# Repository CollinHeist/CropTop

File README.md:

# CropTop
## Development
CropTop is a small-form data acquisition platform initially developed by Kennedy Caisley and Ryan Donahue, two undergraduate electrical engineering students at the University of Idaho. It is designed to support the cereal grain crop strength research being conducted by [Dr. Daniel Roberston](https://www.uidaho.edu/engr/departments/me/our-people/faculty/daniel-robertson) in the UI Department of Mechanical Engineering.

The current iteration of the project is being developed by [Collin Heist](https://github.com/CollinHeist), an undergraduate Electrical Engineering student at University of Idaho.

## What can CropTop do? 
Croptop is based around a 32 bit PIC32MX795F512L microcontroller and includes the following peripherals onboard:

* 12 bit temperature/humidity sensor
* 3-axis accelerometer
* ΔΣ 24 bit 1kSPS ADC
* GNSS receiver
* USB 2.0 OTG interface
* 5A DC motor controller
* Resistive touch controller
* Rotary encoder interface
* Linear encoder interface
* 1GB NAND flash
* User programmable push buttons
* User programmable LEDs
* 14 additional GPIO

The current screen and GUI utilizes the __[Nextion NX8048T070](https://nextion.tech/datasheets/nx8048t070/)__, which has an on-board graphical processor and memory. Interaction with the screen is done through a UART connection. The GUI is created using the Nextion GUI Editor, and has on-board code that can be interacted with using the Nextion-provided commands.

---

## To-Do

- [ ] Finish GPS implementation within `screen.c` and `GPS.c`
    - The interaction with the GPS is inside `screen.c`, but commented out. This is because the PIC would error during GPS read operations, and I was unable to diagnose why. I've since made some changes to the GPS library, and it might work but should be verified before implemented.
- [ ] Finish __refresh_live_feed__ command implementation in `screen.c`.
    - X-Load string needs to be generated and sent to display.
    - Y-Load string needs to be generated and sent to display.
    - Potentiometer angle string needs to be generated and sent to display.
    - IMU angle string needs to be generated and sent to display.
- [ ] Finish __start_test__ command implementation in `screen.c`.
    - The entire test procedure is not implemented.
    - Using `tests.c` is recommended, so that the test library is more comprehensive.
- [ ] Implement __stop_test__ command within `screen.c`.
    - Most likely, a FSM will need to be implemented to reflect the current _state_ of the PIC - i.e. __not_testing__, and __testing__ states inside `tests.c` to facilitate tests.
- [ ] Implement __view_first_folder__ command within `screen.c`.
    - This function will need to sent folder information data to the display. Currently not implemented since USB reading / writing is nonfunctional.
- [ ] Implement __view_next_folder__ command within `screen.c`.
    - This function will need to act similarly to __view_first_folder__, except sequence through folders on the USB.
- [ ] Implement test result graphing on the display.
    - This will need to be done with the `add` and `addt` commands (sent from PIC to display) for writing to the test results Waveform (graph). Read the Nextion Instruction Set description for more detail: https://nextion.tech/instruction-set/ .

---

## PCB Layout

### Version 1.0

Initial PCB design by Kennedy Caisley and Ryan Donahue.

### Version 2.0

Updated PCB design also by Kennedy Caisley and Ryan Donahue. This was more debuggable, and was designed to fit to the screen layout being used at the time (hence the shape). Had all the proper external connectors required for end-use. The screen connectors ended up being incorrectly aligned, and this required changing screen modules.

### Version 3.0

Latest PCB design, by Collin Heist, that removed the on-board graphics chip in favor of the Nextion 7" display header - but otherwise, the design from [v2.0](#pcb-v2) was preserved. The board was expanded to match the mounting holes provided by the Nextion screen.

---

## Code Development Standards

### Development Checklists

#### Header File

- [x] Has a valid file heading ([template](#templates-file-heading)).
- [x] Has multiple-inclusion protection ([template](#templates-inclusion-protection)).
- [x] Has verbose `#define` statements.
- [x] Has function prototypes.
- [x] Has limited (to no) macro functions - replace these with `inline` functions, instead.

#### Source File

- [x] Has an associated header file.
- [x] Has a valid file heading ([template](#templates-file-heading)).
- [x] Has required source file sections ([template](#templates-source-file-sections)).
- [x] All functions have an associated comment block ([template](#templates-source-file-sections)).
- [x] All _small_ functions, that will likely not require stepping through or debugging, are `inline`.
- [x] All function names and variables are verbose (i.e. `initialize_screen()` as opposed to `init_scr()`).
- [x] All function parameters that do not change during operation are `const`.
- [x] All functions that are not user-facing (from a library perspective) are private (`static`).

#### Nextion GUI

- [x] The number of unique pages are kept to a minimum because pages have quite a lot of overhead (in memory).
- [x] Objects with strings - either for text display or variables - have the minimum length required.
- [x] The number of PIC-screen communications are kept to a minimum this is because the UART communication is _somewhat_ unreliable.

-----

### Templates
#### File Heading (source and header)

```C
/**
 *  File
 *      filename.h
 *  Summary
 *      A brief summary of the header file's purpose.
 *  Author(s)
 *      Author 1, Author 2.
 *  Note
 *      Optional additional information regarding the file.
 */
```

#### Multiple Inclusion Protection

```C
#ifndef __FILENAME_H__
    #define __FILENAME_H__
    // Code
#endif
```

#### Source File Sections

```C
/* ----------------------------------- File Inclusion ----------------------------------- */
/* -------------------------- Global Variables and Structures --------------------------- */
/* ---------------------------------- Public Functions ---------------------------------- */
/* --------------------------------- Private Functions ---------------------------------- */
/* ----------------------------- Interrupt Service Routines ----------------------------- */
```

#### Function Comment Blocks

```C
/*
 *  Summary
 *      Short description of the function.
 *  Parameters
 *      param1[in]: Description of the first parameter (in if not changed).
 *      param2[out]: Description of the second parameter (out if changed).
 *  Returns
 *      Describe the meaning of the return value (if there is one).
 *  Note
 *      Optional addition of the function.
 */
```

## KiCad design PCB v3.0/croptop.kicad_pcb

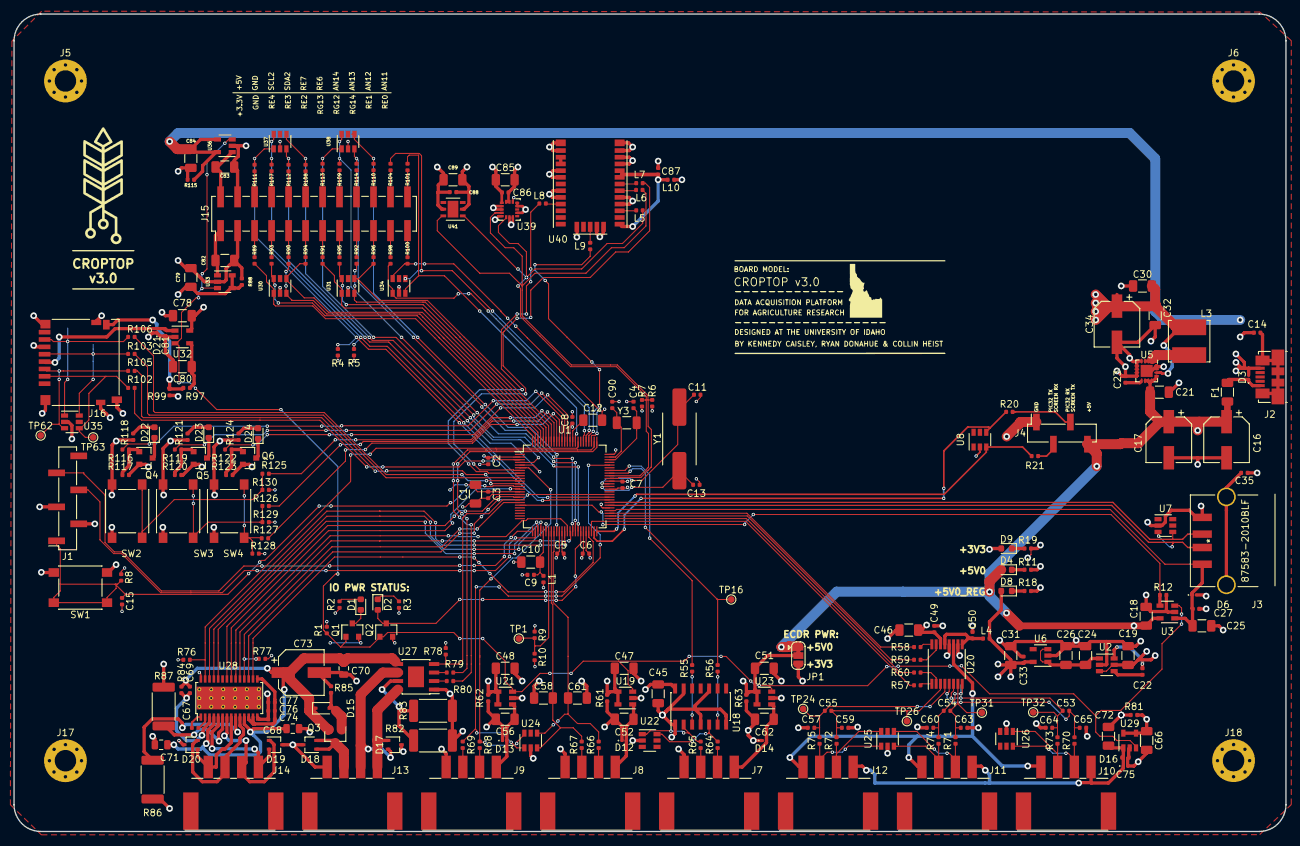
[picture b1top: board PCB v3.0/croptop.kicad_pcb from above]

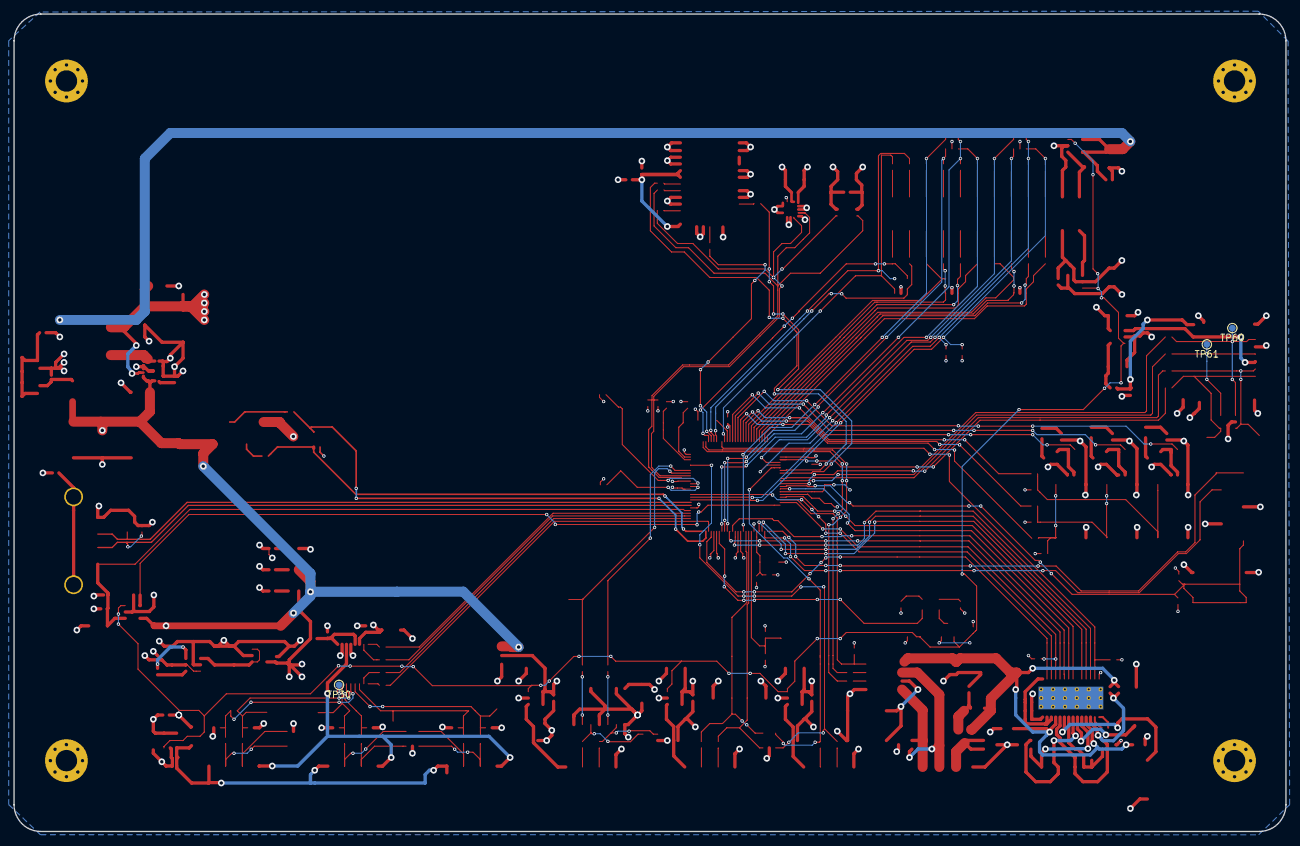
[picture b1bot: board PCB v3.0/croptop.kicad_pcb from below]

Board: 4 copper layers, 190.1 x 122.2 mm, 274 parts (3 on the bottom side), 196 nets.

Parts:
 : idaho
C1, C10, C12, C18, C19, C21, C24, C25, C26, C30, C31, C32, C45, C46, C47, C48, C51, C52, C56, C58, C61, C62, C66, C72, C78, C79, C80, C82, C83, C84, C85, C89: 10u; C_1206_3216Metric
C2, C3, C5, C6, C7, C8, C9, C14, C15, C22, C23, C27, C33, C35, C49, C50, C53, C54, C55, C57, C59, C60, C63, C64, C65, C69, C74, C75, C76, C77, C81, C86, C87, C88: 0.1u; C_0402_1005Metric
C4, C90: 12.5p; C_0402_1005Metric
C11, C13: 27p; C_0402_1005Metric
C16, C17, C34, C73: 100u; CP_Elec_6.3x7.7
C67: 0.01u; C_0402_1005Metric
C68, C70, C71: 0.1u; C_0805_2012Metric
D1, D4, D8, D9, D22, D23, D24: LTSTC190KGKT; LED_0603_1608Metric
D2: LTSTC190KRKT; LED_0603_1608Metric
D3, D6, D12, D13, D14, D16, D21: TPD1E6B06; D_0201_0603Metric
D15: NSR0240HT1G; D_SOD-323
D17, D18, D19, D20: TPD2E007; SOT-323_SC-70
F1: MF-NSMF110; Fuse_1206_3216Metric
J1: TSM-106-01-L-SV; PinHeader_1x06_P2.54mm_Vertical_SMD_Pin1Right
J2: 0473460001; USB_Micro-B_Molex_47346-0001
J3: 87583-2010BLF
J4: NREC004SABC-M30RC; PinHeader_1x04_P2.54mm_Vertical_SMD_Pin1Right
J5, J6, J17, J18: Conn_01x01; MountingHole_3.2mm_M3_Pad_Via
J7, J8, J9, J10, J11, J12, J13, J14: 1702474; solderless_terminal
J15: TSM-112-01-L-DV; PinHeader_2x12_P2.54mm_Vertical_SMD
J16: DM3D-SF; microSD_HC_Hirose_DM3D-SF
JP1: Solder Jumper; SolderJumper-3_P1.3mm_Bridged12_RoundedPad1.0x1.5mm
L1, L4, L10: BKP1005HS121; L_0402_1005Metric
L3: 2.2u; L_Bourns_SRN6045TA
L5, L6, L7, L8, L9: BLM15HD102SN1D; L_0402_1005Metric
Q1, Q4, Q5, Q6: BSS138; SOT-23
Q2: BSS84; SOT-23
Q3: Q2319ADS-T1-GE3; SOT-23
R1, R4, R5, R6, R7, R8, R9, R10, R12, R61, R62, R63, R76, R77, R78, R81, R85, R88, R99, R115, R117, R120, R123, R125, R126, R127, R128, R129, R130: 10k; R_0402_1005Metric
R2, R3, R19, R70, R71, R72, R73, R74, R75, R116, R118, R119, R121, R122, R124: 100; R_0402_1005Metric
R11, R18, R20, R21, R64, R65, R66, R67, R68, R69, R89, R90, R91, R92, R93, R94, R95, R96, R97, R98, R100, R101, R104, R107, R108, R109, R110, R111, R112, R113, R114: 220; R_0402_1005Metric
R55, R56, R57, R58, R59, R60, R79, R80, R102, R103, R105, R106: 22; R_0402_1005Metric
R82, R83, R86, R87: 0.2; R_2512_6332Metric
R84: 1M; R_0402_1005Metric
SW1, SW2, SW3, SW4: SW_Push; SW_SPST_PTS645
TP1, TP16, TP24, TP26, TP30, TP31, TP32, TP60, TP61, TP62, TP63: TestPoint; TestPoint_Pad_D1.0mm
U1: PIC32MX795F512L; TQFP-100_12x12mm_P0.4mm
U2: REG71055DDC; SOT-23-6
U3, U19, U21, U23, U29, U32, U33, U36: AP22802AW5; SOT-23-5
U5: TPS62131RGT; QFN-16-1EP_3x3mm_P0.5mm_EP1.8x1.8mm
U6: TPS70950DBV; SOT-23-5
U7, U8, U22, U24, U25, U26, U30, U31, U34, U35, U37, U38: TPD4E1U06DBV; SOT-23-6
U18: 74HCT125D653; SOIC-14_3.9x8.7mm_P1.27mm
U20: AD7799; TSSOP-16_4.4x5mm_P0.65mm
U27: DRV8872; 8-PowerSOIC
U28: DRV8825; HTSSOP-28-1EP_4.4x9.7mm_P0.65mm_EP3.4x9.5mm_Mask2.4x6.17mm_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
U39: LIS3DSHTR; LISDR
U40: CAM-M8C-0; GPS
U41: Si7006-A20; SI7006
Y1: ABLS-8.000MHZ-B4-T; ABLS_OX
Y3: ABS07-32.768KHZ-1-T; ABLS_SEC

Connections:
+3V3: C1.1, C2.1, C3.1, C5.1, C6.1, C7.1, C8.1, C30.1, C32.1, C34.1, C45.1, C46.1, C47.1, C48.1, C49.1, C78.1, C79.1, C85.1, C86.1, C88.1, C89.1, D9.2, J1.2, J16.10, JP1.3, L1.1, L3.1, L10.1, Q2.2, R1.1, R2.2, R4.1, R5.1, R6.1, R7.1, R8.1, R9.1, R61.1, R62.1, R76.1, R77.1, R78.1, R88.1, R118.2, R121.2, R124.2, SW2.2, SW3.2, SW4.2, U1.2, U1.16, U1.37, U1.46, U1.55, U1.62, U1.86, U5.14, U18.14, U19.4, U19.5, U20.14, U21.4, U21.5, U32.5, U33.4, U33.5, U39.1, U39.7, U39.8, U39.14, U41.5
+5V: C16.1, C17.1, C18.1, C19.1, C21.1, C84.1, D4.2, F1.1, J4.4, JP1.1, R115.1, U2.3, U2.5, U3.5, U5.10, U5.11, U5.12, U5.13, U36.4, U36.5
+5V_REG: C31.1, C33.1, C66.1, D8.2, L4.2, R81.1, U6.5, U29.4, U29.5
ADI_A1+: J10.2, R70.1, U26.6
ADI_A1-: J10.3, R73.1, U26.1
ADI_A2+: J11.2, R71.1, U25.4
ADI_A2-: J11.3, R74.1, U25.3
ADI_A3+: J12.2, R72.1, U25.6
ADI_A3-: J12.3, R75.1, U25.1
ADI_MISO: R59.2, U1.52
ADI_MOSI: R58.2, U1.53
ADI_PSW: J10.4, J11.4, J12.4, U20.11
ADI_SCLK: R57.2, U1.48
CONFIG_ADC: R9.2, R10.1, TP1.1, U1.32
DC_PWM_1: R79.2, U1.76
DC_PWM_2: R80.2, U1.77
DEBUG_BTN_1: R125.1, U1.92
DEBUG_BTN_2: R126.1, U1.91
DEBUG_BTN_3: R127.1, U1.90
DEBUG_LED_1: R116.1, U1.89
DEBUG_LED_2: R119.1, U1.88
DEBUG_LED_3: R122.1, U1.87
DGND: C1.2, C2.2, C3.2, C4.2, C5.2, C6.2, C7.2, C8.2, C9.2, C10.2, C11.2, C12.2, C13.2, C14.2, C15.2, C16.2, C17.2, C18.2, C19.2, C21.2, C23.2, C24.2, C25.2, C26.2, C27.2, C30.2, C31.2, C32.2, C33.2, C34.2, C35.1, C45.2, C46.2, C47.2, C48.2, C49.2, C50.2, C51.2, C52.2, C56.2, C57.1, C58.2, C59.1, C60.1, C61.2, C62.2, C63.1, C64.1, C65.1, C66.2, C68.2, C70.2, C71.2, C72.2, C73.2, C74.2, C75.1, C76.2, C77.2, C78.2, C79.2, C80.2, C81.2, C82.2, C83.2, C84.2, C85.2, C86.2, C87.2, C88.2, C89.2, C90.2, D3.2, D6.2, D12.1, D13.1, D14.1, D16.2, D17.3, D18.3, D19.3, D20.3, D21.1, J1.3, J2.5, J3.4, J4.1, J5.1, J6.1, J7.4, J8.4, J9.4, J13.4, J15.3, J15.4, J16.6, J16.11, J17.1, J18.1, Q1.2, Q4.2, Q5.2, Q6.2, R3.2, R10.2, R11.2, R12.2, R18.2, R19.2, R61.2, R62.2, R63.2, R81.2, R82.2, R83.2, R85.2, R86.2, R87.2, R88.2, R99.2, R115.2, R117.2, R120.2, R123.2, R128.2, R129.2, R130.2, SW1.2, U1.15, U1.31, U1.36, U1.45, U1.65, U1.75, U2.2, U3.2, U5.4, U5.5, U5.6, U5.7, U5.8, U5.15, U5.16, U5.17, U6.2, U7.2, U8.2, U18.1, U18.4, U18.7, U18.10, U18.13, U19.2, U20.10, U20.12, U21.2, U22.2, U23.2, U24.2, U25.2, U26.2, U27.1, U28.14, U28.28, U29.2, U30.2, U31.2, U32.2, U33.2, U34.2, U35.2, U36.2, U37.2, U38.2, U39.2, U39.3, U39.5, U39.10, U39.12, U39.13, U39.15, U39.16, U40.4, U40.5, U40.10, U40.11, U40.12, U40.13, U40.14, U40.15, U40.18, U40.19, U40.21, U40.22, U40.27, U40.30, U40.31, U41.2
ENCDR_A: R56.2, TP16.1, U1.68
ENCDR_B: R55.2, U1.69
GPS_EXTINT: L7.1, U1.7
GPS_PPS: L9.1, U1.79
unnamed: C4.1, U1.73, Y3.1
unnamed: C9.1, C10.1, L1.2, U1.30
unnamed: C11.1, U1.64, Y1.2
unnamed: C12.1, U1.85
unnamed: C13.1, U1.63, Y1.1
unnamed: C14.1, J2.6
unnamed: C22.1, U2.6
unnamed: C22.2, U2.4
unnamed: C23.1, U5.9
unnamed: C24.1, C26.1, U2.1, U6.1, U6.3
unnamed: C35.2, J3.5
unnamed: C50.1, L4.1, U20.9, U20.13
unnamed: C51.1, JP1.2, R63.1, U23.4, U23.5
unnamed: C52.1, D12.2, J8.1, U19.1
unnamed: C53.1, C64.2, R73.2, TP32.1, U20.6
unnamed: C53.2, C65.2, R70.2, U20.5
unnamed: C54.1, C60.2, R74.2, TP30.1, U20.8
unnamed: C54.2, C63.2, R71.2, TP31.1, U20.7
unnamed: C55.1, C57.2, R75.2, TP24.1, U20.4
unnamed: C55.2, C59.2, R72.2, TP26.1, U20.3
unnamed: C56.1, D13.2, J9.1, U21.1
unnamed: C62.1, D14.2, J7.1, U23.1
unnamed: C67.1, U28.2
unnamed: C67.2, U28.1
unnamed: C68.1, C69.2, C70.1, C71.1, C73.1, D15.1, Q3.2, R84.1, U27.5, U28.4, U28.11
unnamed: C69.1, R84.2, U28.3
unnamed: C72.1, C75.2, D16.1, J10.1, J11.1, J12.1, U29.1
unnamed: C74.1, C76.1, C77.1, U28.12, U28.13, U28.15
unnamed: C80.1, R97.2, U32.4
unnamed: C81.1, D21.2, J16.4, U32.1
unnamed: C82.1, J15.1, U33.1
unnamed: C83.1, J15.2, U36.1
unnamed: C87.1, L10.2, U40.1, U40.8, U40.9
unnamed: C90.1, U1.74, Y3.2
unnamed: D1.1, Q1.3
unnamed: D1.2, R2.1
unnamed: D2.1, R3.1
unnamed: D2.2, Q2.3, U1.44
unnamed: D3.1, F1.2, J2.1
unnamed: D4.1, R11.1
unnamed: D8.1, R18.1
unnamed: D9.1, R19.1
unnamed: D15.2, Q3.1, R85.1
unnamed: D17.1, J13.1, U27.8
unnamed: D17.2, J13.2, U27.6
unnamed: D18.1, D18.2, J13.3, Q3.3
unnamed: D19.1, J14.2, U28.7
unnamed: D19.2, J14.1, U28.5
unnamed: D20.1, J14.4, U28.8
unnamed: D20.2, J14.3, U28.10
unnamed: D22.1, Q4.3
unnamed: D22.2, R118.1
unnamed: D23.1, Q5.3
unnamed: D23.2, R121.1
unnamed: D24.1, Q6.3
unnamed: D24.2, R124.1
unnamed: J4.2, R21.2
unnamed: J4.3, R20.2
unnamed: J7.2, R64.1
unnamed: J7.3, R65.1
unnamed: J8.2, R66.1
unnamed: J8.3, R67.1
unnamed: J9.2, R68.1
unnamed: J9.3, R69.1
unnamed: J15.5, R89.2
unnamed: J15.6, R111.2
unnamed: J15.7, R93.2
unnamed: J15.8, R107.2
unnamed: J15.9, R90.2
unnamed: J15.10, R112.2
unnamed: J15.11, R94.2
unnamed: J15.12, R108.2
unnamed: J15.13, R91.2
unnamed: J15.14, R113.2
unnamed: J15.15, R95.2
unnamed: J15.16, R109.2
unnamed: J15.17, R92.2
unnamed: J15.18, R114.2
unnamed: J15.19, R96.2
unnamed: J15.20, R110.2
unnamed: J15.21, R98.2
unnamed: J15.22, R104.2
unnamed: J15.23, R100.2
unnamed: J15.24, R101.2
unnamed: J16.2, R102.1, TP63.1, U35.4
unnamed: J16.3, R105.1, TP62.1, U35.3
unnamed: J16.5, R103.1, TP61.1, U35.6
unnamed: J16.7, R106.1, TP60.1, U35.1
unnamed: J16.9, R97.1, R99.1
unnamed: L3.2, U5.1, U5.2, U5.3
unnamed: L5.2, U40.3
unnamed: L6.2, U40.6
unnamed: L7.2, U40.7
unnamed: L8.2, U40.23
unnamed: L9.2, U40.29
unnamed: Q4.1, R116.2, R117.1
unnamed: Q5.1, R119.2, R120.1
unnamed: Q6.1, R122.2, R123.1
unnamed: R55.1, U18.3
unnamed: R56.1, U18.6
unnamed: R57.1, U20.1
unnamed: R58.1, U20.16
unnamed: R59.1, U20.15
unnamed: R60.1, U20.2
unnamed: R64.2, U18.5, U22.6
unnamed: R65.2, U18.2, U22.1
unnamed: R79.1, U27.3
unnamed: R80.1, U27.2
unnamed: R82.1, R83.1, U27.7
unnamed: R86.1, U28.9
unnamed: R87.1, U28.6
unnamed: R125.2, R130.1, SW2.1
unnamed: R126.2, R129.1, SW3.1
unnamed: R127.2, R128.1, SW4.1
unnamed: U40.16, U40.17
ONBRD_SCL: L6.1, R6.2, U1.66, U39.4, U41.6
ONBRD_SDA: L5.1, R7.2, U1.67, U39.6, U41.1
PICKIT_MCLR: C15.1, J1.1, R8.2, SW1.1, U1.13
PICKIT_PGEC: J1.5, U1.26
PICKIT_PGED: J1.4, U1.27
PMOD_ADC_1: R110.1, U1.35, U38.4
PMOD_ADC_2: R114.1, U1.41, U38.3
PMOD_ADC_3: R109.1, U1.42, U38.6
PMOD_ADC_4: R113.1, U1.43, U38.1
PMOD_CN_1: R101.1, U1.84, U34.3
PMOD_CN_2: R104.1, U1.80, U34.4
PMOD_GPIO_1: R96.1, U1.93, U31.4
PMOD_GPIO_2: R92.1, U1.94, U31.3
PMOD_GPIO_3: R95.1, U1.95, U31.6
PMOD_GPIO_4: R91.1, U1.96, U31.1
PMOD_GPIO_5: R94.1, U1.97, U30.4
PMOD_GPIO_6: R90.1, U1.98, U30.3
PMOD_GPIO_7: R93.1, U1.99, U30.6
PMOD_GPIO_8: R89.1, U1.100, U30.1
PMOD_GPIO_9: R108.1, U1.4, U37.4
PMOD_GPIO_10: R112.1, U1.5, U37.3
PMOD_PWM_1: R100.1, U1.78, U34.6
PMOD_PWM_2: R98.1, U1.81, U34.1
PMOD_SCL: R4.2, R111.1, U1.58, U37.1
PMOD_SDA: R5.2, R107.1, U1.59, U37.6
POTEN_ADC_1: C61.1, R66.2, U1.34, U24.4
POTEN_ADC_2: C58.1, R67.2, U1.33, U24.3
SCREEN_RX: R20.1, U1.49, U8.4
SCREEN_TX: R21.1, U1.50, U8.3
SD_MISO: R106.2, U1.11
SD_MOSI: R105.2, U1.12
SD_SCLK: R103.2, U1.10
SONIC_ECHO: R69.2, U1.71, U24.1
SONIC_TRIG: R68.2, U1.6, U24.6
STEP_DECAY: U1.40, U28.19
STEP_DIR: U1.39, U28.20
STEP_MODE0: U1.28, U28.24
STEP_MODE1: U1.29, U28.25
STEP_MODE2: U1.38, U28.26
STEP_STEP: U1.17, U28.22
USB_D+: J3.3, U1.57, U7.4
USB_D-: J3.2, U1.56, U7.3
USB_PWR_EN: R12.1, U1.20, U3.4
USB_PWR_SENSE: C25.1, C27.1, D6.1, J3.1, U1.54, U3.1
~ADI_CS: R60.2, U1.51
~DC_FAULT: R78.2, U1.18, U27.4
~GPS_RESET: L8.1, U1.8
~PWR_FAULT: Q1.1, Q2.1, R1.2, U3.3, U19.3, U21.3, U23.3, U29.3, U32.3, U33.3, U36.3
~SD_CS: R102.2, U1.3
~STEP_ENBL: U1.14, U28.21
~STEP_FAULT: R77.2, U1.19, U28.18
~STEP_HOME: R76.2, U1.83, U28.27
~STEP_RESET: U1.60, U28.17
~STEP_SLEEP: U1.47, U28.16

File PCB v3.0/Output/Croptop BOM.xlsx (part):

Reference | Value | Footprint | Datasheet | MPN | Note | Rating
C17 | 100u | Capacitor_SMD:CP_Elec_6.3x7.7 |  | EEE-HC1C101XP
U2 | REG71055DDC | Package_TO_SOT_SMD:SOT-23-6 | http://www.ti.com/lit/ds/symlink/reg71050.pdf | REG71055DDCT
L3 | 2.2u | Inductor_SMD:L_Bourns_SRN6045TA | https://www.bourns.com/docs/Product-Datasheets/SRN8040.pdf | SRN6045TA-2R2Y
C21 | 10u | Capacitor_SMD:C_1206_3216Metric |  | CC1206ZRY5V6BB106
C22 | 0.1u | Capacitor_SMD:C_0402_1005Metric |  | CL05F104ZO5NNNC
C31 | 10u | Capacitor_SMD:C_1206_3216Metric |  | CC1206ZRY5V6BB106
J2 | 473460001 | Connector_USB:USB_Micro-B_Molex_47346-0001 | https://www.amphenol-icc.com/media/wysiwyg/files/drawing/101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 | 473460001 | microUSB B
D9 | LTSTC190KGKT | LED_SMD:LED_0603_1608Metric |  | LTST-C190KGKT
R19 | 100 | Resistor_SMD:R_0402_1005Metric |  | RC0402FR-07100RL
D8 | LTSTC190KGKT | LED_SMD:LED_0603_1608Metric |  | LTST-C190KGKT
R18 | 220 | Resistor_SMD:R_0402_1005Metric |  | CRGCQ0402F220R
C16 | 100u | Capacitor_SMD:CP_Elec_6.3x7.7 |  | EEE-HC1C101XP
C34 | 100u | Capacitor_SMD:CP_Elec_6.3x7.7 |  | EEE-HC1C101XP
D4 | LTSTC190KGKT | LED_SMD:LED_0603_1608Metric |  | LTST-C190KGKT
R11 | 220 | Resistor_SMD:R_0402_1005Metric |  | CRGCQ0402F220R
U5 | TPS62131RGT | Package_DFN_QFN:QFN-16-1EP_3x3mm_P0.5mm_EP1.8x1.8mm | http://www.ti.com/lit/ds/symlink/tps62130.pdf | TPS62131RGTT
C23 | 0.1u | Capacitor_SMD:C_0402_1005Metric |  | CL05F104ZO5NNNC
U6 | TPS70950DBV | Package_TO_SOT_SMD:SOT-23-5 | http://www.ti.com/lit/ds/symlink/tps709.pdf | TPS70950DBVR
C26 | 10u | Capacitor_SMD:C_1206_3216Metric |  | CC1206ZRY5V6BB106
C19 | 10u | Capacitor_SMD:C_1206_3216Metric |  | CC1206ZRY5V6BB106
C24 | 10u | Capacitor_SMD:C_1206_3216Metric |  | CC1206ZRY5V6BB106
C30 | 10u | Capacitor_SMD:C_1206_3216Metric |  | CC1206ZKY5V7BB106 |  | 16V
C32 | 10u | Capacitor_SMD:C_1206_3216Metric |  | CC1206ZRY5V6BB106
C33 | 0.1u | Capacitor_SMD:C_0402_1005Metric |  | CL05F104ZO5NNNC
D3 | TPD1E6B06 | Diode_SMD:D_0201_0603Metric |  | TPD1E6B06DPLR
C1 | 10u | Capacitor_SMD:C_1206_3216Metric |  | CC1206ZRY5V6BB106
C2 | 0.1u | Capacitor_SMD:C_0402_1005Metric |  | CL05F104ZO5NNNC
C3 | 0.1u | Capacitor_SMD:C_0402_1005Metric |  | CL05F104ZO5NNNC
C5 | 0.1u | Capacitor_SMD:C_0402_1005Metric |  | CL05F104ZO5NNNC
C6 | 0.1u | Capacitor_SMD:C_0402_1005Metric |  | CL05F104ZO5NNNC
C7 | 0.1u | Capacitor_SMD:C_0402_1005Metric |  | CL05F104ZO5NNNC
C8 | 0.1u | Capacitor_SMD:C_0402_1005Metric |  | CL05F104ZO5NNNC
C12 | 10u | Capacitor_SMD:C_1206_3216Metric |  | CC1206ZRY5V6BB106
R4 | 10k | Resistor_SMD:R_0402_1005Metric |  | RC0402FR-0710KL
R5 | 10k | Resistor_SMD:R_0402_1005Metric |  | RC0402FR-0710KL
L1 | BKP1005HS121 | Inductor_SMD:L_0402_1005Metric |  | BKP1005HS121-TV
C9 | 0.1u | Capacitor_SMD:C_0402_1005Metric |  | CL05F104ZO5NNNC
C10 | 10u | Capacitor_SMD:C_1206_3216Metric |  | CC1206ZRY5V6BB106
R8 | 10k | Resistor_SMD:R_0402_1005Metric |  | RC0402FR-0710KL
C15 | 0.1u | Capacitor_SMD:C_0402_1005Metric |  | CL05F104ZO5NNNC
J1 | TSM-106-01-L-SV | Connector_PinHeader_2.54mm:PinHeader_1x06_P2.54mm_Vertical_SMD_Pin1Right | http://suddendocs.samtec.com/prints/tsm-1xx-xx-xxx-sv-xx-xxx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 | TSM-106-01-L-SV
SW1 | SW_Push | Button_Switch_SMD:SW_SPST_PTS645 |  | PTS645SM43SMTR92 LFS
R9 | 10k | Resistor_SMD:R_0402_1005Metric |  | RC0402FR-0710KL
R10 | 10k | Resistor_SMD:R_0402_1005Metric |  | RC0402FR-0710KL
J3 | 87583-2010BLF | croptop:87583-2010BLF |  | 87583-2010BLF | USB A
U7 | TPD4E1U06DBV | Package_TO_SOT_SMD:SOT-23-6 | http://www.ti.com/lit/ds/symlink/tpd4e1u06.pdf | TPD4E1U06DBVR
C18 | 10u | Capacitor_SMD:C_1206_3216Metric |  | CC1206ZRY5V6BB106
U3 | AP22802AW5 | Package_TO_SOT_SMD:SOT-23-5 | https://www.diodes.com/assets/Datasheets/AP22802.pdf | AP22802AW5-7
R12 | 10k | Resistor_SMD:R_0402_1005Metric |  | RC0402FR-0710KL
C25 | 10u | Capacitor_SMD:C_1206_3216Metric |  | CC1206ZRY5V6BB106
C27 | 0.1u | Capacitor_SMD:C_0402_1005Metric |  | CL05F104ZO5NNNC
U1 | PIC32MX795F512L | Package_QFP:TQFP-100_12x12mm_P0.4mm | http://www.microchip.com/mymicrochip/filehandler.aspx?ddocna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 | PIC32MX795F512LT-80I/PT
Y1 | ABLS-8.000MHZ-B4-T | croptop:ABLS_OX |  | ABLS-8.000MHZ-B4-T
C13 | 27p | Capacitor_SMD:C_0402_1005Metric |  | C0402C270K5GACTU
C11 | 27p | Capacitor_SMD:C_0402_1005Metric |  | C0402C270K5GACTU
R6 | 10k | Resistor_SMD:R_0402_1005Metric |  | RC0402FR-0710KL
R7 | 10k | Resistor_SMD:R_0402_1005Metric |  | RC0402FR-0710KL
D6 | TPD1E6B06 | Diode_SMD:D_0201_0603Metric |  | TPD1E6B06DPLR
C35 | 0.1u | Capacitor_SMD:C_0402_1005Metric |  | CL05F104ZO5NNNC
C14 | 0.1u | Capacitor_SMD:C_0402_1005Metric |  | CL05F104ZO5NNNC
R1 | 10k | Resistor_SMD:R_0402_1005Metric |  | RC0402FR-0710KL
Q1 | BSS138 | Package_TO_SOT_SMD:SOT-23 |  | BSS138-TP
R2 | 100 | Resistor_SMD:R_0402_1005Metric |  | RC0402FR-07100RL
D1 | LTSTC190KGKT | LED_SMD:LED_0603_1608Metric |  | LTST-C190KGKT
Q2 | BSS84 | Package_TO_SOT_SMD:SOT-23 | ~ | BSS84
D2 | LTSTC190KRKT | LED_SMD:LED_0603_1608Metric |  | LTST-C190KRKT
R3 | 100 | Resistor_SMD:R_0402_1005Metric |  | RC0402FR-07100RL
F1 | MF-NSMF110 | Fuse:Fuse_1206_3216Metric | ~ | MF-NSMF110-2
Y3 | ABS07-32.768KHZ-1-T | croptop:ABLS_SEC | https://www.digikey.com/product-detail/en/abracon-llc/ABS07-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 | ABS07-32.768KHZ-1-T
C4 | 12.5p | Capacitor_SMD:C_0402_1005Metric |  | CC0402JRNPO9BN120
C90 | 12.5p | Capacitor_SMD:C_0402_1005Metric |  | CC0402JRNPO9BN120
J4 | NREC004SABC-M30RC | Connector_PinHeader_2.54mm:PinHeader_1x04_P2.54mm_Vertical_SMD_Pin1Right | https://drawings-pdf.s3.amazonaws.com/11657.pdf | NREC004SABC-M30RC
U8 | TPD4E1U06DBV | Package_TO_SOT_SMD:SOT-23-6 | http://www.ti.com/lit/ds/symlink/tpd4e1u06.pdf | TPD4E1U06DBVR
R20 | 220 | Resistor_SMD:R_0402_1005Metric |  | CRGCQ0402F220R
R21 | 220 | Resistor_SMD:R_0402_1005Metric |  | CRGCQ0402F220R
U27 | DRV8872 | croptop:8-PowerSOIC | http://www.ti.com/lit/ds/symlink/drv8872.pdf | DRV8872DDAR
C46 | 10u | Capacitor_SMD:C_1206_3216Metric |  | CC1206ZRY5V6BB106
C49 | 0.1u | Capacitor_SMD:C_0402_1005Metric |  | CL05F104ZO5NNNC
U20 | AD7799 | Package_SO:TSSOP-16_4.4x5mm_P0.65mm | https://www.analog.com/media/en/technical-documentation/data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 | AD7799BRUZ
C50 | 0.1u | Capacitor_SMD:C_0402_1005Metric |  | CL05F104ZO5NNNC
C59 | 0.1u | Capacitor_SMD:C_0402_1005Metric |  | CL05F104ZO5NNNC
C63 | 0.1u | Capacitor_SMD:C_0402_1005Metric |  | CL05F104ZO5NNNC
C60 | 0.1u | Capacitor_SMD:C_0402_1005Metric |  | CL05F104ZO5NNNC
C65 | 0.1u | Capacitor_SMD:C_0402_1005Metric |  | CL05F104ZO5NNNC
C64 | 0.1u | Capacitor_SMD:C_0402_1005Metric |  | CL05F104ZO5NNNC
C57 | 0.1u | Capacitor_SMD:C_0402_1005Metric |  | CL05F104ZO5NNNC
C70 | 0.1u | Capacitor_SMD:C_0805_2012Metric |  | C0805C104Z5VACTU
D15 | NSR0240HT1G | Diode_SMD:D_SOD-323 |  | NSR0240HT1G
C73 | 100u | Capacitor_SMD:CP_Elec_6.3x7.7 |  | UWT1V101MCL1GS |  | 35V
C67 | 0.01u | Capacitor_SMD:C_0402_1005Metric | https://www.digikey.com/product-detail/en/samsung-electro-me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 | CC0402KRX7R9BB103 |  | 50V
R78 | 10k | Resistor_SMD:R_0402_1005Metric |  | RC0402FR-0710KL
R79 | 22 | Resistor_SMD:R_0402_1005Metric |  | RC0402FR-0722RL
R80 | 22 | Resistor_SMD:R_0402_1005Metric |  | RC0402FR-0722RL
R85 | 10k | Resistor_SMD:R_0402_1005Metric |  | RC0402FR-0710KL
R76 | 10k | Resistor_SMD:R_0402_1005Metric |  | RC0402FR-0710KL
R77 | 10k | Resistor_SMD:R_0402_1005Metric |  | RC0402FR-0710KL
R60 | 22 | Resistor_SMD:R_0402_1005Metric |  | RC0402FR-0722RL
R59 | 22 | Resistor_SMD:R_0402_1005Metric |  | RC0402FR-0722RL
R58 | 22 | Resistor_SMD:R_0402_1005Metric |  | RC0402FR-0722RL
R57 | 22 | Resistor_SMD:R_0402_1005Metric |  | RC0402FR-0722RL
R70 | 100 | Resistor_SMD:R_0402_1005Metric |  | RC0402FR-07100RL
R73 | 100 | Resistor_SMD:R_0402_1005Metric |  | RC0402FR-07100RL
R71 | 100 | Resistor_SMD:R_0402_1005Metric |  | RC0402FR-07100RL
R74 | 100 | Resistor_SMD:R_0402_1005Metric |  | RC0402FR-07100RL
R72 | 100 | Resistor_SMD:R_0402_1005Metric |  | RC0402FR-07100RL
R75 | 100 | Resistor_SMD:R_0402_1005Metric |  | RC0402FR-07100RL
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
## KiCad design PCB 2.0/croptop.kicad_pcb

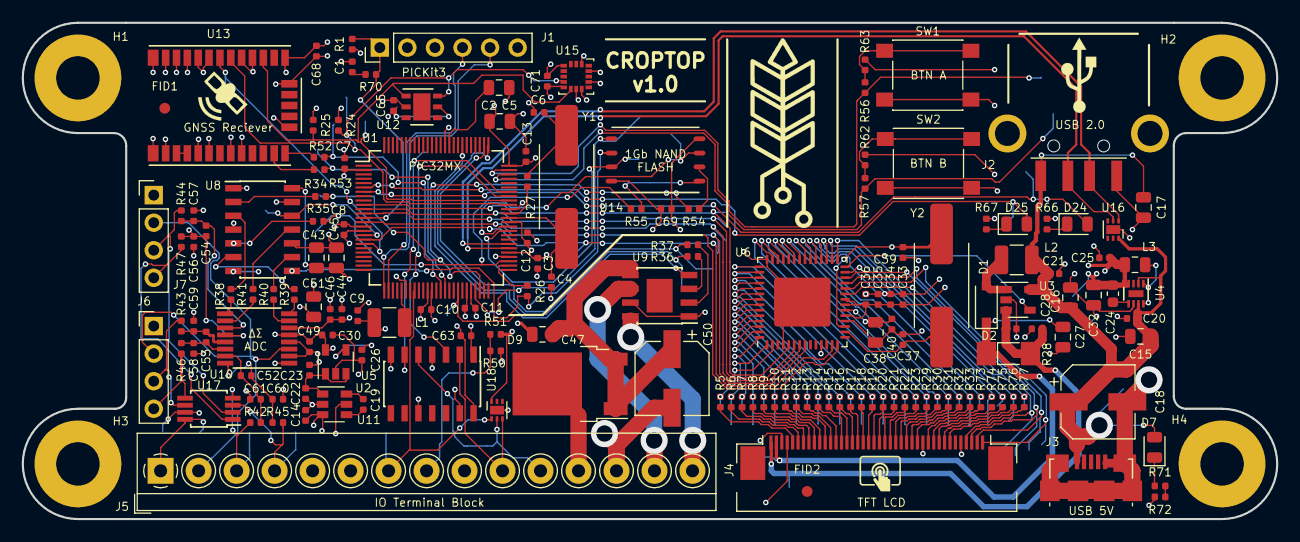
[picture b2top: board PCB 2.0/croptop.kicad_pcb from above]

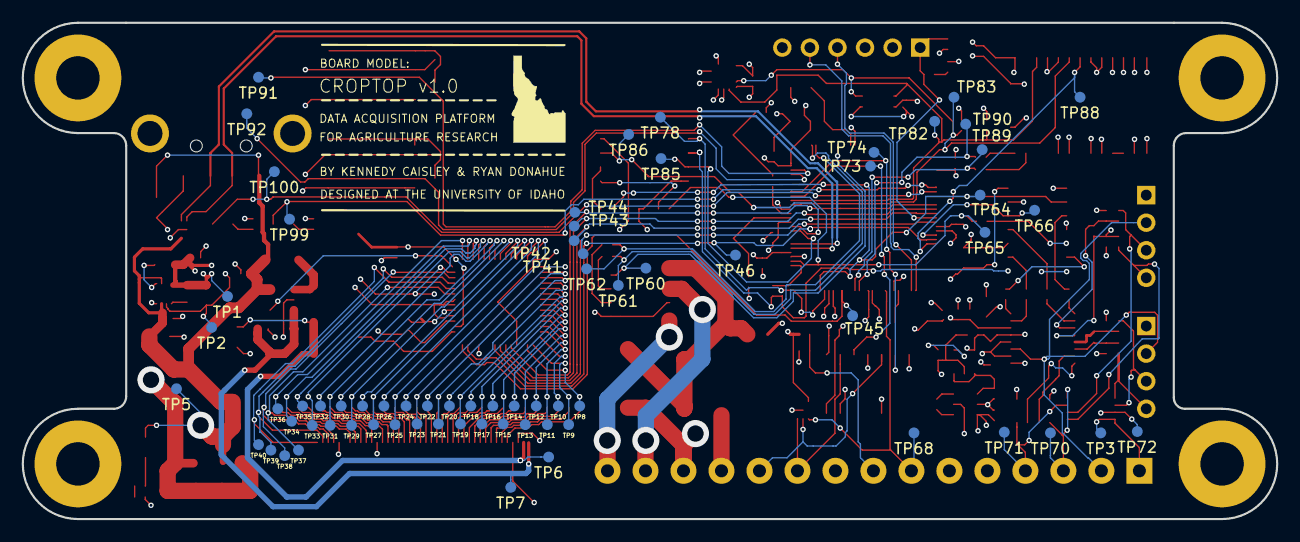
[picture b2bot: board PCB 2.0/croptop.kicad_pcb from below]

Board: 4 copper layers, 115.6 x 45.7 mm, 236 parts (69 on the bottom side), 162 nets.

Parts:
C1, C3, C7, C8, C9, C10, C11, C12, C13, C19, C20, C21, C25, C28, C33, C34, C35, C36, C40, C44, C46, C49, C52, C53, C54, C56, C57, C58, C59, C60, C61, C63, C65, C68, C69, C71: 0.1uF; C_0402_1005Metric
C2, C5, C15, C16, C17, C32, C38, C43, C45, C51: 10uF; C_0805_2012Metric
C4, C6, C37, C39: 26pF; C_0402_1005Metric
C14, C22, C23, C30: 1uF; C_0402_1005Metric
C18, C50: 100uF; CP_Elec_6.3x7.7
C24: 560pF; C_0603_1608Metric
C26: 470pF; C_0402_1005Metric
C27, C47: 0.1uF; C_0805_2012Metric
D1: BAT42W; D_SOD-123
D2: 3SMAJ5935B; DO-214AC
D7, D25: LED1; LED_0805_2012Metric
D9: SBRD10200TR; SizeOfThisLad
D24: LED2; LED_0805_2012Metric
FID1, FID2: FIDUCIAL; Fiducial_1mm_Dia_2.54mm_Outer_CopperTop
H1: Top Left; MountingHole_4mm_Pad
H2: Bottom Left; MountingHole_4mm_Pad
H3: Top Right; MountingHole_4mm_Pad
H4: Bottom Right; MountingHole_4mm_Pad
J1: PICKit Header; PinHeader_1x06_P2.54mm_Vertical
J2: USB_A; USB_A_Assmann_Horizontal
J3: 5V USB; USB_Micro-B_Molex_47346-0001
J4: 4-1734839-0
J5: Terminal Block; TerminalBlock_4Ucon_1x15_P3.50mm_Horizontal
J6, J7: DNP; PinHeader_1x04_P2.54mm_Vertical
L1, L2: 10uH; L_1210_3225Metric
L3: 1uH; L_0805_2012Metric
R1, R56, R57, R62, R63: 10k; R_0402_1005Metric
R5, R6, R7, R8, R9, R10, R11, R12, R13, R14, R15, R16, R17, R18, R19, R20, R21, R22, R23, R29, R30, R31, R32, R33, R73, R74, R75, R76, R77: 33; R_0402_1005Metric
R24, R25: 2K; R_0402_1005Metric
R26, R34, R35, R36, R37, R54, R55: 10; R_0402_1005Metric
R27, R50, R51, R70: 0; R_0402_1005Metric
R28: 2.2; R_0402_1005Metric
R38, R39, R40, R41, R42, R43, R44, R45, R46, R47, R72: 100; R_0402_1005Metric
R52, R53: 220; R_0402_1005Metric
R66, R67, R71: 60; R_0402_1005Metric
SW1, SW2: BTNA; SW_SPST_PTS645
TP1, TP2, TP3, TP5, TP6, TP7, TP8, TP9, TP10, TP11, TP12, TP13, TP14, TP15, TP16, TP17, TP18, TP19, TP20, TP21, TP22, TP23, TP24, TP25, TP26, TP27, TP28, TP29, TP30, TP31, TP32, TP33, TP34, TP35, TP36, TP37, TP38, TP39, TP40, TP41, TP42, TP43, TP44, TP45, TP46, TP60, TP61, TP62, TP64, TP65, TP66, TP68, TP70, TP71, TP72, TP73, TP74, TP78, TP82, TP83, TP85, TP86, TP88, TP89, TP90, TP91, TP92, TP99, TP100: TestPoint_Alt; TestPoint
U1: PIC32MX795F512L; TQFP-100_12x12mm_P0.4mm
U2: REG71055; SOT-23-6
U3: FAN5333BSX; SOT-23-5
U4: MIC23050; DFN-8-1EP_2x2mm_P0.45mm_EP0.64x1.38mm
U5: TC1014; SOT-23-5
U6: FT812Q; QFN-56-1EP_8x8mm_P0.5mm_EP4.5x5.2mm
U8, U11: 74HCT125D; SOIC-14_3.9x8.7mm_P1.27mm
U9: DRV8872; 8-PowerSOIC
U10: AD7799; TSSOP-16_4.4x5mm_P0.65mm
U12: Si7006-A20; SI7006
U13: UCAM-M8Q; GPS
U14: W25N01GV
U15: LIS3DH; LGA-16_3x3mm_P0.5mm_LayoutBorder3x5y
U16, U18: PUSBM5V5X4
U17: DT6250-06MR-13; MSOP-8_3x3mm_P0.65mm
Y1: CXO; ABLS_OX
Y2: 12MHz; ABLS_OX

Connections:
ADC_A1+: J5.3, R42.1, TP70.1, U17.4
ADC_A1-: J5.4, R45.1, TP71.1, U17.3
ADC_CS: TP66.1, U1.17, U8.12
ADC_GND: J5.2, J6.2, J7.2, U10.11
ADC_VDD: C30.1, C49.1, C51.1, J5.1, J6.1, J7.1, TP3.1, U5.5, U10.9, U10.13, U17.8
BTN_A: R56.1, TP91.1, U1.74
BTN_B: R57.1, TP92.1, U1.73
DRV_BAT: D9.2, J5.12
DRV_FLT: TP60.1, U1.82, U9.4
DRV_GND: C1.2, C2.2, C3.2, C4.2, C5.2, C6.2, C7.2, C8.2, C9.2, C10.2, C11.2, C12.2, C13.2, C14.2, C15.2, C16.2, C17.2, C18.2, C20.2, C21.2, C22.2, C23.2, C25.2, C26.2, C27.2, C28.2, C30.2, C32.2, C33.2, C34.2, C35.2, C36.2, C37.2, C38.2, C39.2, C40.2, C43.2, C44.2, C45.2, C46.2, C47.2, C49.2, C50.2, C51.2, C56.1, C57.1, C58.1, C59.1, C60.1, C61.1, C63.2, C65.2, C68.2, C69.2, C71.2, J1.3, J2.4, J2.5, J3.5, J3.6, J4.3, J4.29, J4.36, J5.6, J5.9, J5.13, R28.2, R62.2, R63.2, R66.1, R67.1, R72.2, TP2.1, TP72.1, U1.15, U1.31, U1.36, U1.45, U1.65, U1.75, U2.2, U3.2, U4.6, U4.8, U5.2, U6.4, U6.18, U6.27, U6.42, U6.57, U8.1, U8.4, U8.7, U8.10, U8.13, U9.1, U9.7, U10.10, U10.12, U11.1, U11.4, U11.7, U11.10, U11.13, U12.2, U13.4, U13.5, U13.10, U13.11, U13.12, U13.13, U13.14, U13.15, U13.18, U13.19, U13.21, U13.22, U13.27, U13.31, U14.4, U15.5, U15.10, U15.12, U16.7, U17.7, U18.7
DRV_IN1: R36.2, TP61.1, U1.76
DRV_IN2: R37.2, TP62.1, U1.77
DRV_OUT1: J5.14, U9.6
DRV_OUT2: J5.15, U9.8
DVDD: C3.1, C5.1, C7.1, C8.1, C9.1, C10.1, C11.1, C12.1, C13.1, C24.2, C25.1, C32.1, C33.1, C34.1, C35.1, C36.1, C43.1, C44.1, C45.1, C46.1, C63.1, C65.1, C68.1, C69.1, C71.1, J1.2, J4.4, J5.5, L1.1, L3.1, R1.1, R24.1, R25.1, R50.1, SW1.2, SW2.2, TP1.1, U1.2, U1.16, U1.37, U1.46, U1.55, U1.62, U1.86, U4.4, U6.11, U6.19, U6.21, U6.22, U8.14, U10.14, U11.14, U12.5, U13.1, U13.8, U13.9, U14.8, U15.1, U15.7, U15.8, U15.14
DVDD_UNREG: C14.1, C15.1, C16.1, C17.1, C18.1, C20.1, C21.1, D7.2, J2.1, J3.1, L2.2, R51.2, TP5.1, U1.54, U2.3, U2.5, U3.5, U4.2, U4.7, U16.6, U18.6
GPS_INT: TP88.1, U1.19, U13.7
LCD_ANODE: C27.1, D1.1, D2.1, J4.2, TP6.1
LCD_B0: R21.2, TP24.1, U6.41
LCD_B1: R22.2, TP25.1, U6.40
LCD_B2: R23.2, TP26.1, U6.39
LCD_B3: R29.2, TP27.1, U6.38
LCD_B4: R30.2, TP28.1, U6.37
LCD_B5: R31.2, TP29.1, U6.36
LCD_B6: R32.2, TP30.1, U6.35
LCD_B7: R33.2, TP31.1, U6.34
LCD_CATHODE: C28.1, D2.2, J4.1, R28.1, TP7.1, U3.3
LCD_DEN: R77.2, TP36.1, U6.29
LCD_DISP: R74.2, TP33.1, U6.32
LCD_G0: R13.2, TP16.1, U6.50
LCD_G1: R14.2, TP17.1, U6.49
LCD_G2: R15.2, TP18.1, U6.48
LCD_G3: R16.2, TP19.1, U6.47
LCD_G4: R17.2, TP20.1, U6.46
LCD_G5: R18.2, TP21.1, U6.45
LCD_G6: R19.2, TP22.1, U6.44
LCD_G7: R20.2, TP23.1, U6.43
LCD_HSYNC: R75.2, TP35.1, U6.31
LCD_INT: TP46.1, U1.18, U6.13
LCD_PD: TP45.1, U1.43, U6.14
LCD_PWM: U3.4, U6.28
LCD_R0: R5.2, TP8.1, U6.2
LCD_R1: R6.2, TP9.1, U6.1
LCD_R2: R7.2, TP10.1, U6.56
LCD_R3: R8.2, TP11.1, U6.55
LCD_R4: R9.2, TP12.1, U6.54
LCD_R5: R10.2, TP13.1, U6.53
LCD_R6: R11.2, TP14.1, U6.52
LCD_R7: R12.2, TP15.1, U6.51
LCD_SHIFT: R73.2, TP32.1, U6.33
LCD_VSYNC: R76.2, TP34.1, U6.30
LED_A: D25.2, TP99.1, U1.6
LED_B: D24.2, TP100.1, U1.7
LIN_IN: J5.7, TP68.1, U1.33, U18.1
MISO: R26.1, U8.8, U14.2
MOSI: R35.2, R55.2, TP65.1, U1.53
NAND_CS: TP78.1, U1.47, U14.1
NAND_HOLD: TP86.1, U1.61, U14.7
NAND_WP: TP85.1, U1.60, U14.3
unnamed: C1.1, R70.1
unnamed: C2.1, U1.85
unnamed: C4.1, U1.63, Y1.2
unnamed: C6.1, R27.1, Y1.1
unnamed: C19.1, U2.6
unnamed: C19.2, U2.4
unnamed: C22.1, C23.1, U2.1, U5.1, U5.3
unnamed: C24.1, U4.5
unnamed: C26.1, U5.4
unnamed: C37.1, U6.16, Y2.1
unnamed: C38.1, C40.1, U6.20
unnamed: C39.1, U6.17, Y2.2
unnamed: C47.1, C50.1, D9.1, U9.5
unnamed: C52.1, C61.2, R42.2, U10.7
unnamed: C52.2, C60.2, R45.2, U10.8
unnamed: C53.1, C59.2, R43.2, U10.5
unnamed: C53.2, C58.2, R46.2, U10.6
unnamed: C54.1, C57.2, R44.2, U10.3
unnamed: C54.2, C56.2, R47.2, U10.4
unnamed: D1.2, L2.1, U3.1
unnamed: D7.1, R71.1
unnamed: D24.1, R66.2
unnamed: D25.1, R67.2
unnamed: J4.5, R5.1
unnamed: J4.6, R6.1
unnamed: J4.7, R7.1
unnamed: J4.8, R8.1
unnamed: J4.9, R9.1
unnamed: J4.10, R10.1
unnamed: J4.11, R11.1
unnamed: J4.12, R12.1
unnamed: J4.13, R13.1
unnamed: J4.14, R14.1
unnamed: J4.15, R15.1
unnamed: J4.16, R16.1
unnamed: J4.17, R17.1
unnamed: J4.18, R18.1
unnamed: J4.19, R19.1
unnamed: J4.20, R20.1
unnamed: J4.21, R21.1
unnamed: J4.22, R22.1
unnamed: J4.23, R23.1
unnamed: J4.24, R29.1
unnamed: J4.25, R30.1
unnamed: J4.26, R31.1
unnamed: J4.27, R32.1
unnamed: J4.28, R33.1
unnamed: J4.30, R73.1
unnamed: J4.31, R74.1
unnamed: J4.32, R75.1
unnamed: J4.33, R76.1
unnamed: J4.34, R77.1
unnamed: J6.3, R43.1, U17.6
unnamed: J6.4, R46.1, U17.5
unnamed: J7.3, R44.1, U17.2
unnamed: J7.4, R47.1, U17.1
unnamed: L1.2, U1.30
unnamed: L3.2, U4.1
unnamed: R26.2, U1.52
unnamed: R27.2, U1.64
unnamed: R34.1, U8.2
unnamed: R35.1, U8.5
unnamed: R36.1, U9.3
unnamed: R37.1, U9.2
unnamed: R38.1, U10.1
unnamed: R38.2, U8.3
unnamed: R39.1, U10.16
unnamed: R39.2, U8.6
unnamed: R40.1, U10.15
unnamed: R40.2, U8.9
unnamed: R41.1, U10.2
unnamed: R41.2, U8.11
unnamed: R52.1, U13.25
unnamed: R53.1, U13.26
unnamed: R54.1, U14.6
unnamed: R55.1, U14.5
unnamed: R56.2, R63.1, SW1.1
unnamed: R57.2, R62.1, SW2.1
unnamed: R71.2, R72.1
unnamed: U13.16, U13.17
PKT_MCLR: J1.1, R1.2, R70.2, U1.13
PKT_PGEC: J1.5, U1.26
PKT_PGED: J1.4, U1.27
ROT_A1: J5.10, U11.2, U18.3
ROT_A2: J5.11, U11.5, U18.2
ROT_VDD: J5.8, R50.2, R51.1
ROT_Y1: TP73.1, U1.68, U11.3
ROT_Y2: TP74.1, U1.69, U11.6
RX: R53.2, TP90.1, U1.39
SCL: R24.2, TP83.1, U1.66, U12.6, U13.6, U15.4
SCLK: R34.2, R54.2, TP64.1, U1.48
SCLK2: TP44.1, U1.10, U6.5
SDA: R25.2, TP82.1, U1.67, U12.1, U13.3, U15.6
SDIO2: TP43.1, U1.11, U6.6
SDO2: TP42.1, U1.12, U6.7
SS2: TP41.1, U1.14, U6.8
TCH_DOWN: J4.38, TP38.1, U6.26
TCH_LEFT: J4.39, TP39.1, U6.25
TCH_RIGHT: J4.37, TP37.1, U6.23
TCH_UP: J4.40, TP40.1, U6.24
TX: R52.2, TP89.1, U1.40
USB_D+: J2.3, U1.57, U16.1
USB_D-: J2.2, U1.56, U16.2

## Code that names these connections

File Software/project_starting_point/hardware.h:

/**
 *	File
 *		hardware.h
 *	Summary
 *		Shared hardware header file. Gives useful macros for error-handling, switch operation,
 *		LED toggling, and system timings.
 *	Author(s)
 *		Collin Heist
 */

#ifndef __HARDWARE_H__
	#define __HARDWARE_H__

	// Macros for error-detection
	#define NO_ERROR				(0)
	#define ERROR					(1)
	#define TRUE					(1)
	#define FALSE					(0)

	// Shared Pin Configurations
	#define DEBUG_BTN_2_PIN			(BIT_7)		// DEBUG_BTN_1 is Pin 92, RA7
	#define DEBUG_BTN_2_PORT		(IOPORT_A)
	#define DEBUG_BTN_3_PIN			(BIT_6)		// DEBUG_BTN_2 is Pin 91, RA6
	#define DEBUG_BTN_3_PORT		(IOPORT_A)
	#define DEBUG_BTN_4_PIN			(BIT_0)		// DEBUG_BTN_3 is Pin 90, RG0
	#define DEBUG_BTN_4_PORT		(IOPORT_G)
	#define DEBUG_LED_1_PIN			(BIT_1)		// DEBUG_LED_1 is Pin 89, RG1
	#define DEBUG_LED_1_PORT		(IOPORT_G)
	#define DEBUG_LED_2_PIN			(BIT_1)		// DEBUG_LED_2 is Pin 91, RA6
	#define DEBUG_LED_2_PORT		(IOPORT_F)
	#define DEBUG_LED_3_PIN			(BIT_0)		// DEBUG_LED_3 is Pin 90, RG0
	#define DEBUG_LED_3_PORT		(IOPORT_F)

	// System timing definitions
	#define SOFTWARE_1MS_COUNT		(8000)

	#define GetSystemClock()		(80000000ul)
	#define GetInstructionClock()	(GetSystemClock() / 2)	
	#define GetPeripheralClock()	(GetSystemClock() / 1)	
	#define CORE_MS_TICK_RATE		(GetInstructionClock() / 1000)

	// Data-type definitions
		// See chapter 8 of the XC32 compiler guide http://ww1.microchip.com/downloads/en/DeviceDoc/50001686J.pdf
	#define NUM_BYTES_SHORT			(2)
	#define NUM_BYTES_INT			(4)
	#define NUM_BYTES_FLOAT			(4)
	
	// Function Prototypes
	unsigned int initialize_shared_hardware(void);
	inline void clear_buffer(char * buffer, const unsigned int length);
	inline void copy_buffer(char * destination, const char * source, const unsigned int length);
	inline void software_delay_ms(const unsigned int milliseconds);
	inline unsigned int read_button2(void);
	inline unsigned int read_button3(void);
	inline unsigned int read_button4(void);
	inline unsigned int read_button2(void);
	inline void toggle_LED1(void);
	inline void toggle_LED2(void);
	inline void toggle_LED3(void);
#endif

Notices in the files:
parts and their libraries:
Copyright 2016 Accelerated Designs. All rights reserved.
